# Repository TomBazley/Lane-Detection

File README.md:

# Lane Detection

A final year BEng electronics project that aims to detect lanes on a road from a live video feed. Using an FPGA, the lanes are detected by applying the sobel operator combined with searching for pixels brighter than a variable threshold.

## Demonstration

https://user-images.githubusercontent.com/62083547/172941356-2ffd6f28-229f-4e7b-8cfc-a31fc2a52e07.mp4

This demonstration shows a recording of the screen which displays the processed video. The red markers are produced by the FPGA to indicate the position of the lane.

## Schematic

A circuit board was designed which includes an iCE40 FPGA, a VGA port for video input, a VGA-to-digital conversion chip, a STM32 microcontroller to configure the FPGA and VGA converter, and a display to view the processed images. The circuit board also features a power supply, overvoltage protection, and reverse polarity protection.

# PCB

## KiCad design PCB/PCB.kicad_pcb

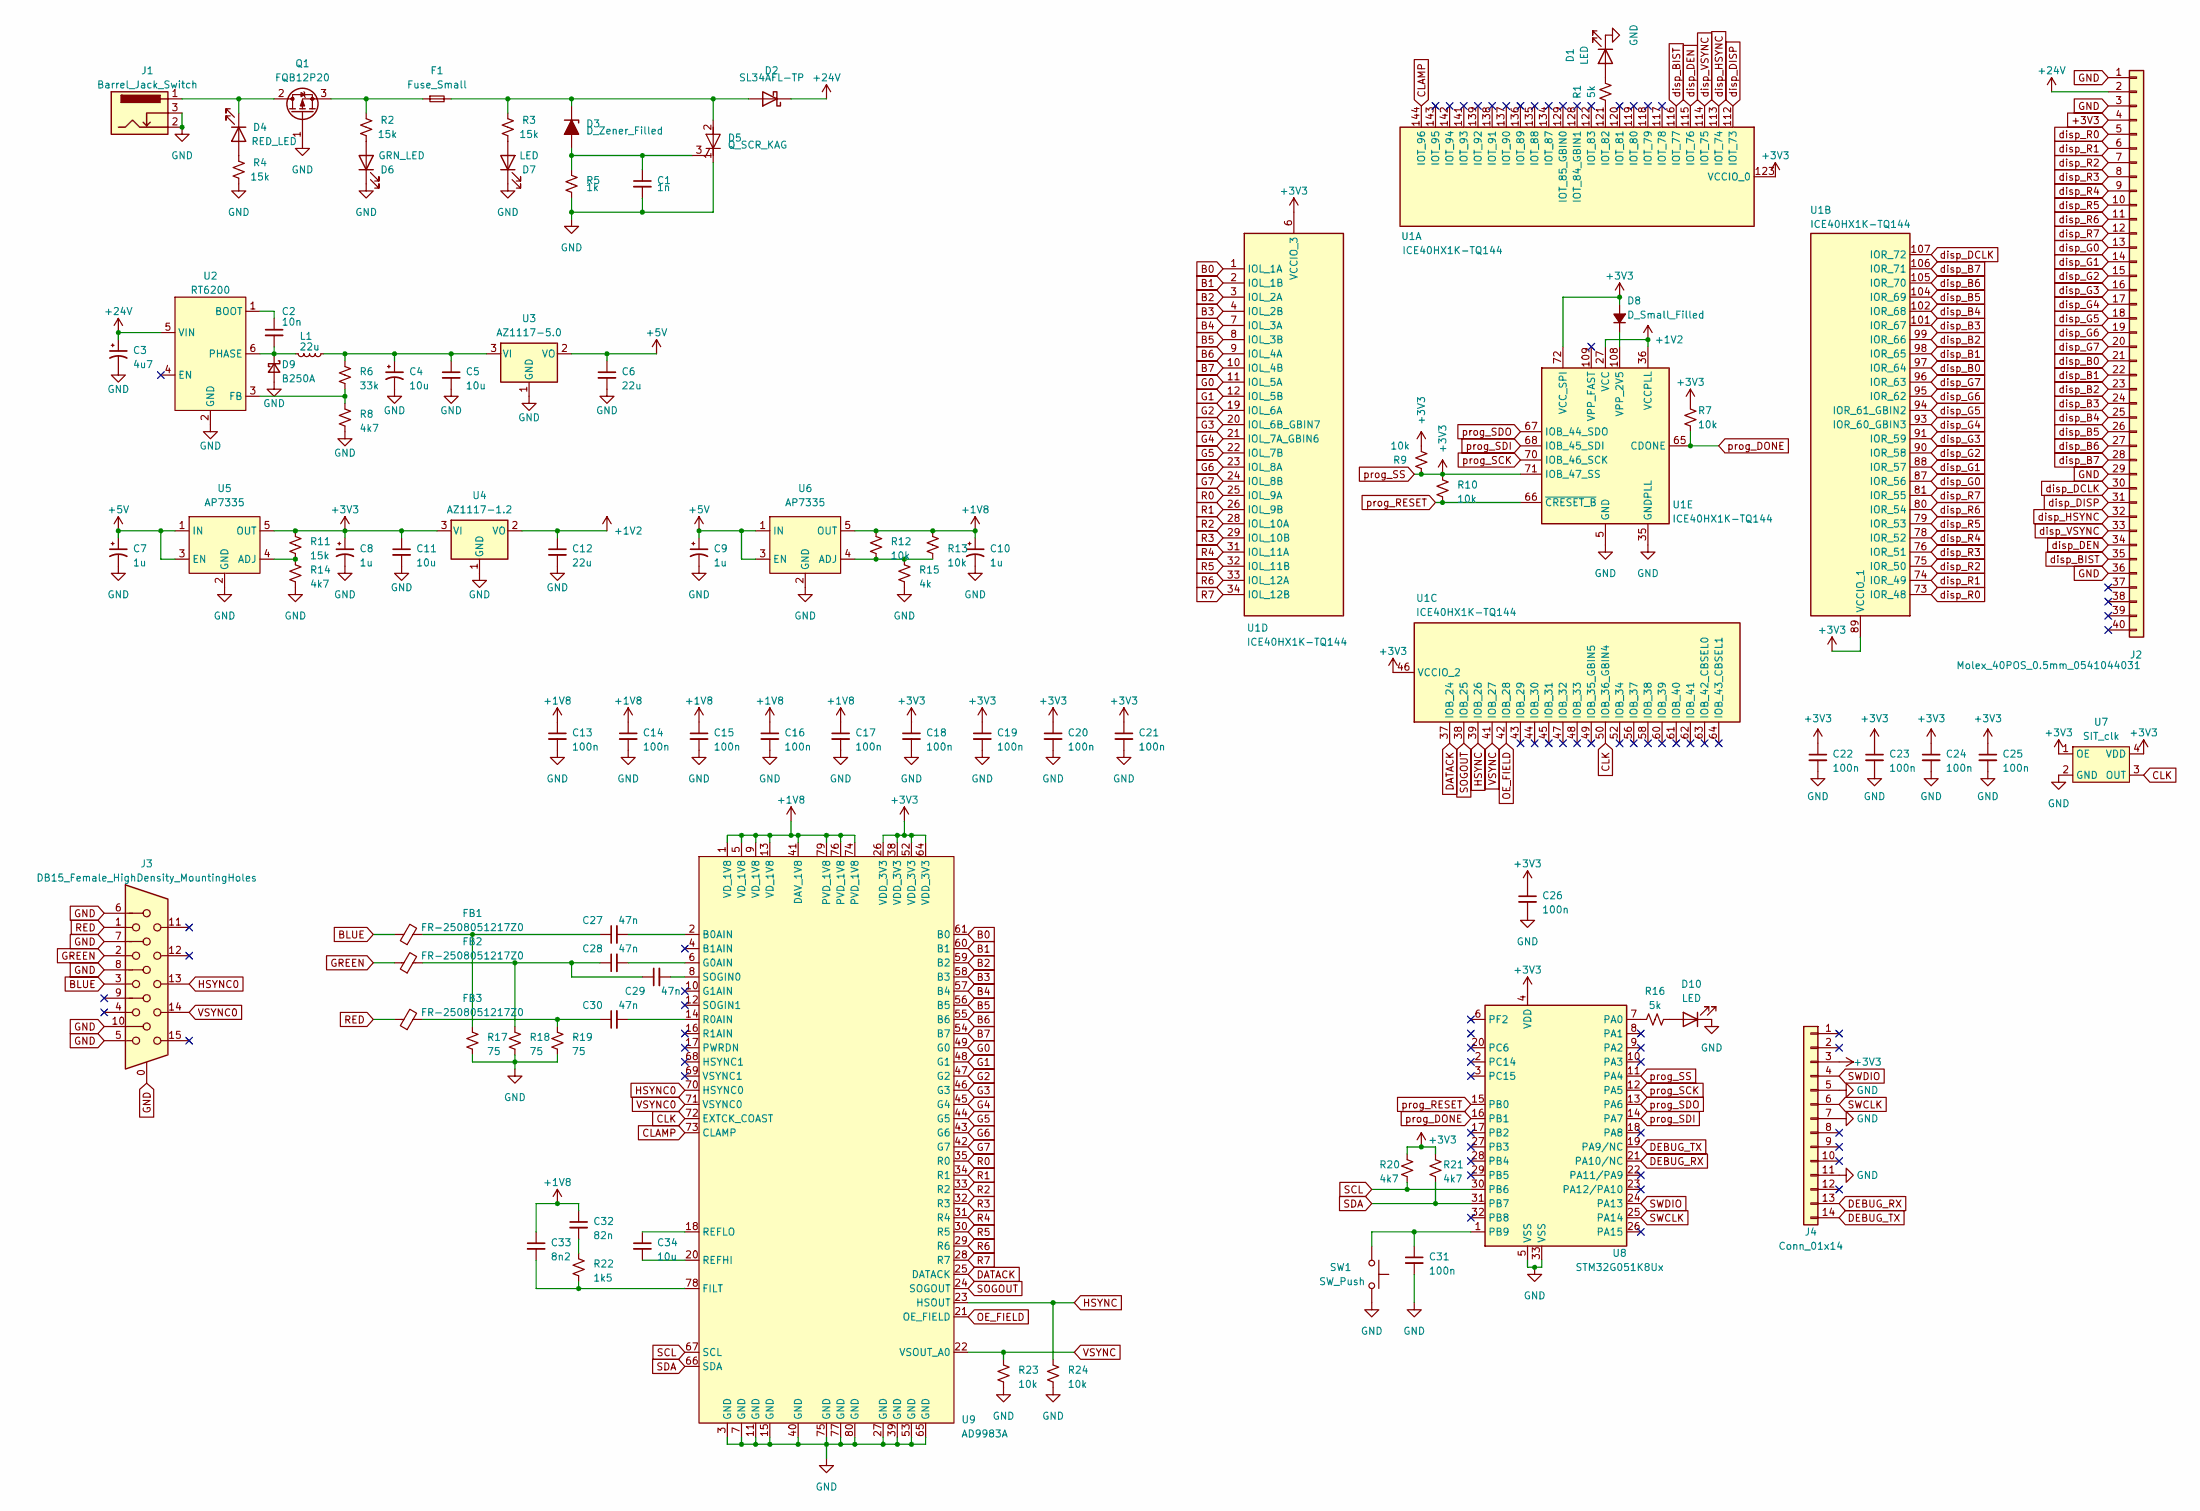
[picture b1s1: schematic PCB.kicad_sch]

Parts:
C1: 1n; C_0805_2012Metric
C2: 10n; C_0805_2012Metric
C3: 4u7; CP_EIA-7343-31_Kemet-D
C4: 10u; CP_EIA-7343-31_Kemet-D
C5, C11, C34: 10u; C_0805_2012Metric
C6, C12: 22u; C_0805_2012Metric
C7, C8, C9, C10: 1u; CP_EIA-3528-21_Kemet-B
C13, C14, C15, C16, C17, C18, C19, C20, C21, C22, C23, C24, C25, C26, C31: 100n; C_0805_2012Metric
C27, C28, C29, C30: 47n; C_0805_2012Metric
C32: 82n; C_0805_2012Metric
C33: 8n2; C_0805_2012Metric
D1, D7, D10: LED; LED_0603_1608Metric
D2: SL34AFL-TP; D_SMA
D3: D_Zener_Filled; D_SOD-123
D4: RED_LED; LED_0603_1608Metric
D5: Q_SCR_KAG; TO-252-2
D6: GRN_LED; LED_0603_1608Metric
D8: D_Small_Filled; D_SOD-123
D9: B250A; D_SMA
F1: Fuse_Small; Fuse_1210_3225Metric
FB1, FB2, FB3: FR-2508051217Z0; L_0805_2012Metric
J1: Barrel_Jack_Switch; Barrel PJ-002BH-SMT-TR
J2: Molex_40POS_0.5mm_0541044031
J3: DB15_Female_HighDensity_MountingHoles; VGA 10090926-P154XLF
J4: Conn_01x14; SAMTECH-FTSH-107-01-F-DV-K
L1: 22u; IHLP2525CZER220M11
Q1: FQB12P20; TO-263-2
R1, R16: 5k; R_0805_2012Metric
R2, R3, R4, R11: 15k; R_0805_2012Metric
R5: 1k; R_0805_2012Metric
R6: 33k; R_0805_2012Metric
R7, R9, R10, R12, R13, R23, R24: 10k; R_0805_2012Metric
R8, R14, R20, R21: 4k7; R_0805_2012Metric
R15: 4k; R_0805_2012Metric
R17, R18, R19: 75; R_0805_2012Metric
R22: 1k5; R_0805_2012Metric
SW1: SW_Push; SW_SPST_PTS645
U1: ICE40HX1K-TQ144; TQFP-144_20x20mm_P0.5mm
U2: RT6200; SOT-23-6
U3: AZ1117-5.0; SOT-223
U4: AZ1117-1.2; SOT-223
U5, U6: AP7335; SOT-23-5
U7: SIT_clk; SIT8008xx-1x
U8: STM32G051K8Ux; QFN-32-1EP_5x5mm_P0.5mm_EP3.45x3.45mm
U9: AD9983A; LQFP-80_14x14mm_P0.65mm

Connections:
+1V2: C12.1, U1.27 (VCC), U1.36 (VCCPLL), U1.51 (VCC), U1.92 (VCC), U1.111 (VCC), U4.2 (VO)
+1V8: C10.1, C13.1, C14.1, C15.1, C16.1, C17.1, C32.1, C33.1, R12.1, R13.1, U6.5 (OUT), U9.1 (VD_1V8), U9.5 (VD_1V8), U9.9 (VD_1V8), U9.13 (VD_1V8), U9.41 (DAV_1V8), U9.74 (PVD_1V8), U9.76 (PVD_1V8), U9.79 (PVD_1V8)
+3V3: C8.1, C11.1, C18.1, C19.1, C20.1, C21.1, C22.1, C23.1, C24.1, C25.1, C26.1, D8.2 (A), J2.4, J4.3, R7.1, R9.1, R9.2, R10.1, R11.1, R20.1, R21.1, U1.6 (VCCIO_3), U1.30 (VCCIO_3), U1.46 (VCCIO_2), U1.57 (VCCIO_2), U1.71 (IOB_47_SS), U1.72 (VCC_SPI), U1.89 (VCCIO_1), U1.100 (VCCIO_1), U1.123 (VCCIO_0), U1.133 (VCCIO_0), U4.3 (VI), U5.5 (OUT), U7.1 (OE), U7.4 (VDD), U8.4 (VDD), U8.11 (PA4), U9.26 (VDD_3V3), U9.38 (VDD_3V3), U9.52 (VDD_3V3), U9.64 (VDD_3V3)
+5V: C6.1, C7.1, C9.1, U3.2 (VO), U5.1 (IN), U5.3 (EN), U6.1 (IN), U6.3 (EN)
+24V: C3.1, D2.1 (K), J2.2, U2.5 (VIN)
B0: U1.1 (IOL_1A), U9.61 (B0)
B1: U1.2 (IOL_1B), U9.60 (B1)
B2: U1.3 (IOL_2A), U9.59 (B2)
B3: U1.4 (IOL_2B), U9.58 (B3)
B4: U1.7 (IOL_3A), U9.57 (B4)
B5: U1.8 (IOL_3B), U9.56 (B5)
B6: U1.9 (IOL_4A), U9.55 (B6)
B7: U1.10 (IOL_4B), U9.54 (B7)
BLUE: FB1.1, J3.3
CLAMP: U1.144 (IOT_96), U9.73 (CLAMP)
CLK: U1.50 (IOB_36_GBIN4), U7.3 (OUT), U9.72 (EXTCK_COAST)
DATACK: U1.37 (IOB_24), U9.25 (DATACK)
DEBUG_RX: J4.13, U8.21 (PA10/NC)
DEBUG_TX: J4.14, U8.19 (PA9/NC)
G0: U1.11 (IOL_5A), U9.49 (G0)
G1: U1.12 (IOL_5B), U9.48 (G1)
G2: U1.19 (IOL_6A), U9.47 (G2)
G3: U1.20 (IOL_6B_GBIN7), U9.46 (G3)
G4: U1.21 (IOL_7A_GBIN6), U9.45 (G4)
G5: U1.22 (IOL_7B), U9.44 (G5)
G6: U1.23 (IOL_8A), U9.43 (G6)
G7: U1.24 (IOL_8B), U9.42 (G7)
GND: C1.2, C3.2, C4.2, C5.2, C6.2, C7.2, C8.2, C9.2, C10.2, C11.2, C12.2, C13.2, C14.2, C15.2, C16.2, C17.2, C18.2, C19.2, C20.2, C21.2, C22.2, C23.2, C24.2, C25.2, C26.2, C31.2, D1.1 (K), D5.1 (K), D6.1 (K), D7.1 (K), D9.2 (A), D10.1 (K), J1.2, J1.3, J2.1, J2.3, J2.29, J2.36, J3.0, J3.5, J3.6, J3.7, J3.8, J3.10, J4.5, J4.7, J4.11, Q1.1 (G), R4.2, R5.2, R8.2, R14.2, R15.2, R17.2, R18.2, R19.2, R23.2, R24.2, SW1.2, U1.5 (GND), U1.13 (GND), U1.14 (GND), U1.35 (GNDPLL), U1.59 (GND), U1.69 (GND), U1.86 (GND), U1.103 (GND), U1.132 (GND), U1.140 (GND), U2.2 (GND), U3.1 (GND), U4.1 (GND), U5.2 (GND), U6.2 (GND), U7.2 (GND), U8.5 (VSS), U8.33 (VSS), U9.3 (GND), U9.7 (GND), U9.11 (GND), U9.15 (GND), U9.27 (GND), U9.39 (GND), U9.40 (GND), U9.53 (GND), U9.65 (GND), U9.75 (GND), U9.77 (GND), U9.80 (GND)
GREEN: FB2.1, J3.2
HSYNC: R24.1, U1.39 (IOB_26), U9.23 (HSOUT)
HSYNC0: J3.13, U9.70 (HSYNC0)
unnamed: C27.1, FB1.2, R17.1
unnamed: C28.1, C29.1, FB2.2, R18.1
unnamed: C30.1, FB3.2, R19.1
unnamed: C32.2, R22.1
unnamed: D1.2 (A), R1.2
unnamed: D2.2 (A), D3.1 (K), D5.2 (A), F1.2, R3.1
unnamed: C1.1, D3.2 (A), D5.3 (G), R5.1
unnamed: D4.2 (A), R4.1
unnamed: D4.1 (K), J1.1, Q1.2 (D)
unnamed: D6.2 (A), R2.2
unnamed: D7.2 (A), R3.2
unnamed: D8.1 (K), U1.108 (VPP_2V5)
unnamed: C2.2, D9.1 (K), L1.1, U2.6 (PHASE)
unnamed: D10.2 (A), R16.2
unnamed: F1.1, Q1.3 (S), R2.1
unnamed: R1.1, U1.121 (IOT_82)
unnamed: C2.1, U2.1 (BOOT)
unnamed: R6.2, R8.1, U2.3 (FB)
unnamed: C4.1, C5.1, L1.2, R6.1, U3.3 (VI)
unnamed: R11.2, R14.1, U5.4 (ADJ)
unnamed: R12.2, R13.2, R15.1, U6.4 (ADJ)
unnamed: R16.1, U8.7 (PA0)
unnamed: C31.1, SW1.1, U8.1 (PB9)
unnamed: C27.2, U9.2 (B0AIN)
unnamed: C33.2, R22.2, U9.78 (FILT)
unnamed: C28.2, U9.6 (G0AIN)
unnamed: C30.2, U9.14 (R0AIN)
unnamed: C34.2, U9.20 (REFHI)
unnamed: C34.1, U9.18 (REFLO)
unnamed: C29.2, U9.8 (SOGIN0)
OE_FIELD: U1.42 (IOB_28), U9.21 (OE_FIELD)
R0: U1.25 (IOL_9A), U9.35 (R0)
R1: U1.26 (IOL_9B), U9.34 (R1)
R2: U1.28 (IOL_10A), U9.33 (R2)
R3: U1.29 (IOL_10B), U9.32 (R3)
R4: U1.31 (IOL_11A), U9.31 (R4)
R5: U1.32 (IOL_11B), U9.30 (R5)
R6: U1.33 (IOL_12A), U9.29 (R6)
R7: U1.34 (IOL_12B), U9.28 (R7)
RED: FB3.1, J3.1
SCL: R20.2, U8.30 (PB6), U9.67 (SCL)
SDA: R21.2, U8.31 (PB7), U9.66 (SDA)
SOGOUT: U1.38 (IOB_25), U9.24 (SOGOUT)
SWCLK: J4.6, U8.25 (PA14)
SWDIO: J4.4, U8.24 (PA13)
VSYNC: R23.1, U1.41 (IOB_27), U9.22 (VSOUT_A0)
VSYNC0: J3.14, U9.71 (VSYNC0)
disp_B0: J2.21, U1.97 (IOR_64)
disp_B1: J2.22, U1.98 (IOR_65)
disp_B2: J2.23, U1.99 (IOR_66)
disp_B3: J2.24, U1.101 (IOR_67)
disp_B4: J2.25, U1.102 (IOR_68)
disp_B5: J2.26, U1.104 (IOR_69)
disp_B6: J2.27, U1.105 (IOR_70)
disp_B7: J2.28, U1.106 (IOR_71)
disp_BIST: J2.35, U1.116 (IOT_77)
disp_DCLK: J2.30, U1.107 (IOR_72)
disp_DEN: J2.34, U1.115 (IOT_76)
disp_DISP: J2.31, U1.112 (IOT_73)
disp_G0: J2.13, U1.87 (IOR_56)
disp_G1: J2.14, U1.88 (IOR_57)
disp_G2: J2.15, U1.90 (IOR_58)
disp_G3: J2.16, U1.91 (IOR_59)
disp_G4: J2.17, U1.93 (IOR_60_GBIN3)
disp_G5: J2.18, U1.94 (IOR_61_GBIN2)
disp_G6: J2.19, U1.95 (IOR_62)
disp_G7: J2.20, U1.96 (IOR_63)
disp_HSYNC: J2.32, U1.113 (IOT_74)
disp_R0: J2.5, U1.73 (IOR_48)
disp_R1: J2.6, U1.74 (IOR_49)
disp_R2: J2.7, U1.75 (IOR_50)
disp_R3: J2.8, U1.76 (IOR_51)
disp_R4: J2.9, U1.78 (IOR_52)
disp_R5: J2.10, U1.79 (IOR_53)
disp_R6: J2.11, U1.80 (IOR_54)
disp_R7: J2.12, U1.81 (IOR_55)
disp_VSYNC: J2.33, U1.114 (IOT_75)
prog_DONE: R7.2, U1.65 (CDONE), U8.16 (PB1)
prog_RESET: R10.2, U1.66 (~CRESET_B), U8.15 (PB0)
prog_SCK: U1.70 (IOB_46_SCK), U8.12 (PA5)
prog_SDI: U1.68 (IOB_45_SDI), U8.14 (PA7)
prog_SDO: U1.67 (IOB_44_SDO), U8.13 (PA6)

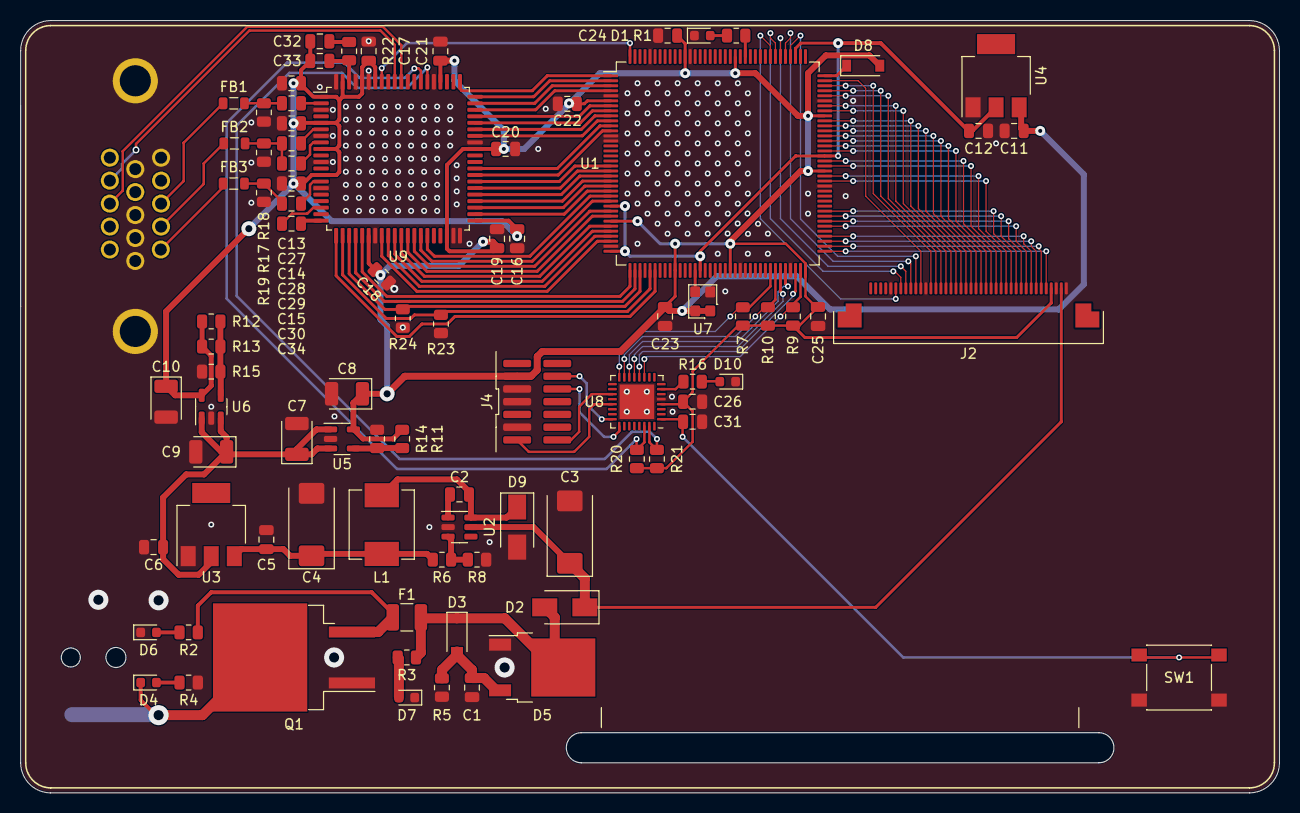
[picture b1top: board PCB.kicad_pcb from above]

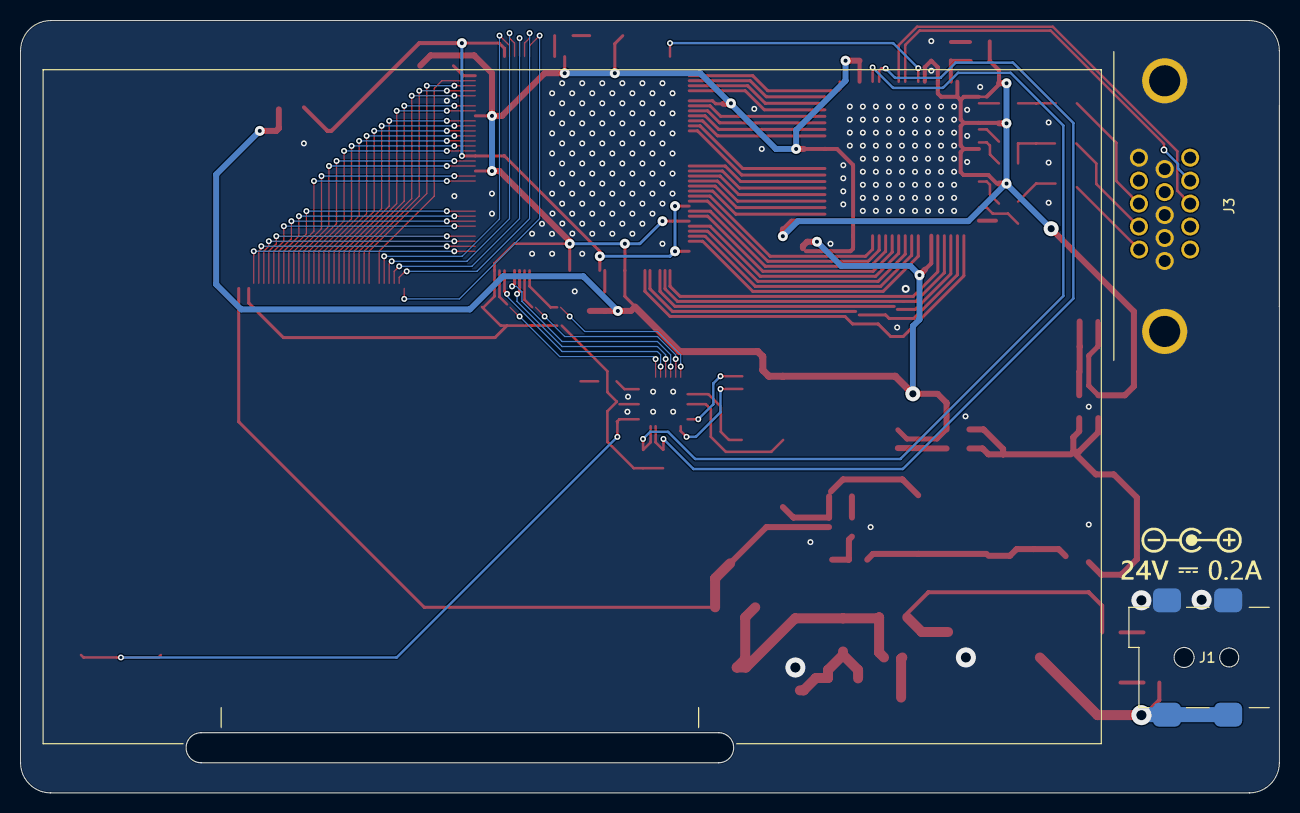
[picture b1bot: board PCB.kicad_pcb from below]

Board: 2 copper layers, 125.5 x 77.0 mm, 88 parts (2 on the bottom side), 113 nets.

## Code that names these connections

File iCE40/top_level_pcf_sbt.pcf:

# ##############################################################################

# iCEcube PCF

# Version:            2020.12.27943

# File Generated:     Apr 4 2022 16:43:52

# Family & Device:    iCE40HX1K

# Package:            TQ144

# ##############################################################################

###IOSet List 2
set_io clk 37

set_io mosi 68
set_io sck 70
set_io cs_n 71

set_io b_in[0] 1
set_io b_in[1] 2
set_io b_in[2] 3
set_io b_in[3] 4
set_io b_in[4] 7
set_io b_in[5] 8
set_io b_in[6] 9
set_io b_in[7] 10
set_io g_in[0] 11
set_io g_in[1] 12
set_io g_in[2] 19
set_io g_in[3] 20
set_io g_in[4] 21
set_io g_in[5] 22
set_io g_in[6] 23
set_io g_in[7] 24
set_io r_in[0] 25
set_io r_in[1] 26
set_io r_in[2] 28
set_io r_in[3] 29
set_io r_in[4] 31
set_io r_in[5] 32
set_io r_in[6] 33
set_io r_in[7] 34
set_io sogout 38
set_io hsync 39
set_io vsync 41
set_io oe_field 42
set_io clamp 144

set_io r_out[0] 73
set_io r_out[1] 74
set_io r_out[2] 75
set_io r_out[3] 76
set_io r_out[4] 78
set_io r_out[5] 79
set_io r_out[6] 80
set_io r_out[7] 81
set_io g_out[0] 87
set_io g_out[1] 88
set_io g_out[2] 90
set_io g_out[3] 91
set_io g_out[4] 93
set_io g_out[5] 94
set_io g_out[6] 95
set_io g_out[7] 96
set_io b_out[0] 97
set_io b_out[1] 98
set_io b_out[2] 99
set_io b_out[3] 101
set_io b_out[4] 102
set_io b_out[5] 104
set_io b_out[6] 105
set_io b_out[7] 106
set_io disp_clk 107
set_io disp_disp 112
set_io disp_hsync 113
set_io disp_vsync 114
set_io disp_den 115
set_io disp_bist 116

set_io led 121

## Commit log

2022-05-18 Add readme
2022-06-10 Add video and images to README
2022-06-10 Fix binary logic width matching
